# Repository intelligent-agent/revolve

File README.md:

```
    _/_/_/                                    _/                       
   _/    _/    _/_/    _/      _/    _/_/    _/  _/      _/    _/_/    
  _/_/_/    _/_/_/_/  _/      _/  _/    _/  _/  _/      _/  _/_/_/_/   
 _/    _/  _/          _/  _/    _/    _/  _/    _/  _/    _/          
_/    _/    _/_/_/      _/        _/_/    _/      _/        _/_/_/     
                                                                       
```                                                                      

## Main features
- 1GHz Single board solution using [Octavo OSB3358 SIP](https://octavosystems.com/2016/05/09/osd3358-new-era-integration/)
- 6 [TMC2130](https://www.trinamic.com/products/integrated-circuits/details/tmc2130/) stepper drivers, stall detection, overcurrent/temp
- 4 Thermistor or Thermocouple inputs (runtime configurable)
- 4 high power heater outputs
- 4 GB fast eMMC
- Optionally 2 external drivers
- [Direct coupled PRU lines](http://beagleboard.org/pru) to all drivers
- Flexible PWM on all 8 MOSFET outputs for flexible EMC passing
- 4 USB host ports, 1 USB device port
- 10/100Mbit Ethernet
- 1080p HDMI
- Smart power controls
 - Input voltage and current measurement
 - Power removed detection
 - Software defined overcurrent protecion
- Quad encoder input for filament sensor
- Buffered end stop inputs, ESD protected connectors
- 2 Servo outputs
- Inductive sensor input
- Two Grove connectors, I2C and UART

## Power management
Here is an overview of the power distribution

## 5V step down TPS54202 calculations

```python
import math
Vout = 5.1 # Output voltage
Vin = 24 # Input voltage
Iout = 2 # Output current
Kind = 0.3 # ?
Fsw = 500000 # Switching frequency
Cbulk = 10 *10**-6
u = 10**6 # micro

```

```python
L=(Vout*(Vin-Vout))/(Vin*Kind*Iout*Fsw)
print "Inductor selection:"
print "Minimum inductor size: "+str(L*10**6)+" uH"

Lout = 15*10**-6
Ilmax = math.sqrt(Iout**2 + (1/12) + ((Vout*(Vin-Vout))/(Vin*Lout*Fsw*0.8))**2)
print "RMS Inductor current "+str(Ilmax)
Ipeak = Iout + (Vout * (Vin - Vout))/(1.6*Vin*Lout*Fsw)
print "Max inductor current "+str(Ipeak)
print "Choosing NR8040T330M"

```

    Inductor selection:
    Minimum inductor size: 13.3875 uH
    RMS Inductor current 2.10904312204
    Max inductor current 2.3346875
    Choosing NR8040T330M

```python
dIout = 0.7
dVout = 0.2 # Delta voltage with dI
Vr = 0.03 # Ripple Voltage
Ir = Iout*0.3
CO1 = (2*dIout)/(Fsw*dVout)
CO2 = (1.0/(8.0*Fsw))*(1.0/(Vr/Ir))
#CO3 =
print "Input Capacitor Selection:"
print "CO1: "+str(CO1*u) + " uF"
print "CO2: "+str(CO2*u) + " uF"

#print "Minimum capacitance: "+str(CO*u)+" uF"
print "Choosing 20uF"
```

    Input Capacitor Selection:
    CO1: 14.0 uF
    CO2: 5.0 uF
    Choosing 20uF

```python
R2 = 100.0*10**3
R3 = 13.3*10**3
Vref = 0.596
Vout = Vref*((R2/R3)+1)
print "Calculation of output resistance: "
print "Vout = "+str(Vout)
```

    Calculation of output resistance:
    Vout = 5.07720300752

## Stepper drivers

Current sense resistor:

```python
R = 0.1
I = 1
U = R*I
P = U*I
print "Power dissipation: "+str(P)
```

    Power dissipation: 0.1

**Diagnostics:**
```python
$2*8 = 16$
```

* Connect together to form a single interrupt?
No, it's good to have individual pins for stallguard.

## Capacitor selection
- 100uF electrolytic capacitor is recommended. No mention of ESR or ripple current in the TMC2130 data sheet.
- What is the frequency at which the largest current draw is expected?
- There are 10uF capacitors in line to handle high frequency current draws, so it is expected that the electrolytic capacitors will handle lower frequecy draws. It depends on cable length, ESR in PSU as well.

**SPI and enable**  
* Enable pins, can it be done using SPI?
* SPI CS pins, need 8 pins at least.
    * Use Mux?
        * Increased cost. How much?
        *
    * Daisy chain?
        * What is the required time?
        * Not good for Stepper A/B. Use CN1?
        * Each transaction takes 60 us
    * Individual pins.
        * Requires 8 pins.
*

```python
print "Stepper readout time: "
a = 6.0*40/(4*10**6)
print "it takes "+str(a*u)+" us for each transaction"
```

    Stepper readout time:
    it takes 60.0 us for each transaction

## PWM calculations

**Current setting**
* Use PWM chip?
    * Costly > $1
    * board space
* Use internal reference
    * 5 bit precision

```python
print "Number of current steps on TMC2130: "+str(2**5)
```

    Number of current steps on TMC2130: 32

# Smart input current monitor circuit.
Fuses have slow responses, so they do not protect against short circuits
and only asymptotically approach their rating with time. They are temperature dependent, difficult to
replace, and physically large. They also increase manufacturing time and cost due to almost universally being
through-hole components.

 - Measure input voltage
 - Measure input current.
 - Choosing PMOS to also implement power lost detection.
 - Reverse polarity protection

```python
R = 0.001
A = 30
adc_vals = 2**12
v_adc = 1.8
v_res = R*A
Gain = 50
resolution =(v_adc/adc_vals)/R/Gain

print "Over current calculations:"
print "Max current: "+str(A)+" A"
print "Resistor value: "+str(R*1000)+" mOhm"
print "Voltage drop across resistor: "+str(v_res*1000)+" mV"
print "Voltage measured: "+str(v_res*Gain)
print "Power dissipation in Rsense: "+str(R*A*A)+" W"
print "resolution: "+str(resolution*1000)+" mA"
```

    Over current calculations:
    Max current: 30 A
    Resistor value: 1.0 mOhm
    Voltage drop across resistor: 30.0 mV
    Voltage measured: 1.5
    Power dissipation in Rsense: 0.9 W
    resolution: 8.7890625 mA

```python
v_max = 24
R1 = 100*10**3
R2 = 4.7*10**3
print "Input voltage calculations: "
print "Voltage divider max output: "+str(v_max*R2/(R1+R2))
print "Input voltage resolution: ??"
```

    Input voltage calculations:
    Voltage divider max output: 1.07736389685
    Input voltage resolution: ??

```python
Imax = 30
RDS = 5.6*10**-3
Ploss = RDS*Imax*Imax
print "Input P-mos power calculations:"
print "Power expenditure: "+str(Ploss)+ " W"
```

    Input P-mos power calculations:
    Power expenditure: 5.04 W

## ESD considerations
 - EN 55024/EN 61000-4-2: ±4kV Contact, ±8kV Air
### Board
 - Ground shield, having 0.1R to ground.
### USB
 - Using [TPD4S012](http://www.ti.com/product/TPD4S012) having Contact: ±10kV, Air: ±10kV
### HDMI
 - Using [TPD12S016](http://www.ti.com/product/TPD12S016)
### Ethernet
 - Isolated using magnetics.
### Endstops
 - Input buffer [CD4050BD](http://www.ti.com/product/CD4050BD) with HBD: ±1500, CDM: ±1000
### Analog
 - Series resistance
### Steppers
 - TMC2130 HBM: ±4 kV
### Heater MOSFETs
 - 4.7nF protection
### Fan MOSFETS
 - No protection

## Layout considerations
Using en562748 as reference for PHY layout.
 - Using 100R resistors in series to reduce EMI.
 - Placing PHY chip close to SIP since differential lines radiate less than 3.3V single ended lines.
 - Removing ground plane under magnetics.
 - 100 Ohm differential impedance
 - Place 49.9ohm pullups close to PHY chip.
 - OSH park uses FR408 laminate

```python
Er = 3.67 # Relative dielectric costant
H = 0.17018 # prepreg height in mm
T = 0.035 # Copper thickness (mm)
F = 125 # Frequency MHz
print "0.15/0.15 track and gap gives 98.4 differential and 65.3 single ended"
```

    0.15/0.15 track and gap gives 98.4 differential and 65.3 single ended

```python
Vf = 2.8 # Diode forward voltage drop (V)
Vin = 3.3 # Input voltage (V)
Vres = Vin-Vf
If = 0.0001 # Diode current, 1mA
R = Vres/If
print "LED power calculations: "
print "Resistor for {}, {}mA: {}".format(Vin, If*1000,R)
```

    LED power calculations:
    Resistor for 3.3, 0.1mA: 5000.0

# Sysboot config
Two Boot modes: MMC1 or USB device
 - SYSBOOT[15-14] = 10b = 25MHz
 - SYSBOOT[13:12] = 00b = reserved
 - SYSBOOT[11:10] = xx
 - SYSBOOT[9] = xx
 - SYSBOOT[8] = xx
 - SYSBOOT[7-6] = xx
 - SYSBOOT[5] = 0b = Disable CLKOUT1
 - SYSBOOT[4:0] = 11100b = MMC1, MMC0, UART0, USB0

 To boot from USB:
 - SYSBOOT[4:0] = 11000b = SPI0, MMCO0, USB0, UART0

```python
Imax = 1.5 # Maximum output current on all 4 USB ports
Rmeas = 0.01 # Current measurement resistor on low side.
RDSon = 0.065 #P-mos RDSon
Vin = 5.1
Vdrop = Vin - (Rmeas + RDSon)*Imax
print "Voltage drop across R: {}".format(Rmeas*Imax)
print "Resulting voltage to USB: {}".format(Vdrop)
```

    Voltage drop across R: 0.015
    Resulting voltage to USB: 4.9875

```python
Imax = 1.5 # Maximum output current on all 4 USB ports
Rmeas = 0.01 # Current measurement resistor on low side.
RDSon = 0.065 #P-mos RDSon
Vin = 5.1
Vdrop = Vin - (Rmeas + RDSon)*Imax
print "Voltage drop across R: {}".format(Rmeas*Imax)
print "Resulting voltage to USB: {}".format(Vdrop)
```

    Voltage drop across R: 0.015
    Resulting voltage to USB: 4.9875

### Review
 - Changed vias to tented
 - Moved pin 1 indicator on U2
 - Moved all test points to top side
 -

```python
from IPython.display import display, Markdown, Latex
```

## Calculation of power dissipation of P-MOS
* `$R_{ds(on)max} = 45 m\Omega$ @ $-10 V$`
* Thermal Resistance, Junction to Ambient @ `$TA=+25 ^{\circ}C$ is $R_{\theta JA}=26 ^{\circ}C/W$`

```python
Von=6
Ta=25
Imax=30
#Imax=2
Rdson=0.0045
TR=26

# P=I^2*R
P=Imax*Imax*Rdson

Trise=TR*P
T=Ta+Trise

display(Markdown("""
$P={P:0.3f} W$\n
$T_{{rise}} = {Trise} ^{{\circ}}C$\n
$T = T_A + T_{{rise}} = {T:0.3f} ^{{\circ}}C$ when $I={I:.0f} A$

""".format(P=P, Trise=Trise, T=T, I=Imax)))
```

    $P=4.050 W$

    $T_{rise} = 105.3 ^{\circ}C$

    $T = T_A + T_{rise} = 130.300 ^{\circ}C$ when $I=30 A$

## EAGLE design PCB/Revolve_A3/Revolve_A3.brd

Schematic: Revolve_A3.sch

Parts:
C1, C2, C4, C5, C6, C8, C10, C12, C13, C15, C16, C18, C19, C20, C21, C23, C24, C27, C28, C29, C30, C31, C32, C35, C38, C40, C43, C44, C53, C54, C56, C60, C61, C63, C64, C66, C67, C69, C70, C72, C73, C74, C82, C83, C84, C85, C87, C99, C107, C108, C110, C114, C115, C133, C134, C138, C140, C141, C142, C150, C151, C155: 0.1uF; C0402; MPN CL10B104KB8NNND
C3, C7, C9, C11, C39, C88, C132: 22nF; C0402; MPN C1005X7R1E223K050BB
C14, C17, C48, C80: 22uF; C1206; MPN CL31B106KAHNNNE
C22, C57, C58, C59, C102: 4.7nF; C0402; MPN CL05B472KA5NNNC
C25: 100uF; 153CLV-0605; MPN RSL0J101MCN1GB
C26, C33, C37, C45, C46, C49, C55, C65, C68, C86, C103: 4.7uF; C0402; MPN GRM155R60J475ME47D
C34, C109, C111, C112, C113: 2.2uF; C0402; MPN GRM155R61A225KE95D
C36, C146, C147, C148, C149, C156, C157: 18pF; C0402; MPN GRM0335C1E180JA01D
C41, C47, C89, C91, C92, C93, C100: 10uF,35V; C0805; MPN GRM21BR6YA106KE43K
C42, C94, C95, C97, C98, C101: 100uF,35V,0.025R; RHS1V10MCN1GS; MPN RHS1V101MCN1GS
C135, C143: 10uF,3.3V; C0805; MPN C0805C106K8PACTU
C136: 470pF; C0402; MPN CL05B471KB5NNNC
D1, D2, D3, D4, D5: MBRA340T3; SMA; MPN MBRA340T3G
EEPROM_WP: TPB1,27; B1,27
IC1, IC6, IC7: 74AHC1G126DCK; SC70-5; MPN M74VHC1GT126DF1G
IC2: CY7C65632; QFN28; MPN CY7C65632-28LTXCT
IC29: LAN8710A; 32-QFN; MPN LAN8710A-EZC-TR
IC30: MTFC2GMDEA; WFBGA; MPN EMMC04G-M627-X03R
J1: CTI-JTAG
J2, J3: 4P-2.0; HW4-2.0; MPN 1125S-4P
JP1, JP2: FIDUCIAL1X2.5; FIDUCIAL-1X2.5
L1: 15uH; NR8040T330; MPN NRS8040T150MJGJ
L2, L3: 150OHM,800mA; L2012C; MPN MU2029-151Y
LED0, LED1, LED2, LED3, LED4, LED5, LED6, LED7, LED8, LED9, LED10, LED11, LED12, LED13: blue; CHIP-LED0603; MPN 19-217/BHC-ZL1M2RY/3T
LOGO1: OSHW_LOGO_FILLX0200-NT; OSHW_FILLX200_NOTEXT
MGT1, MGT2, MGT3, MGT4: MOUNTING_HOLE
PMIC_NRESET: TPTP10R; TP10R
Q1, Q2, Q3, Q8: AON6758; 8-DFN-EP-(5X6); MPN SIRA34DP-T1-GE3
Q4, Q5, Q6, Q7, Q12: NPN-TRANSISTOR_SOT23; SOT23; MPN AO7400
Q9: MMBT2907; SOT23-BEC; MPN MMBT2907ALT3G
Q10, Q11, Q13, Q14: DMC2038LVT; TSOT26; MPN DMC2038LVT-7
R1, R2, R6, R27, R31, R35, R37, R38, R39, R40, R43, R50, R55, R56, R57, R58, R60, R73, R78, R81, R88, R90, R94, R121, R127, R128, R129, R130, R131, R132, R133, R134, R135, R136, R137, R140, R141, R147, R152: 10K,1%; R0402; MPN RC0402FR-0710KL
R3, R4, R7, R8, R9, R10, R11, R29, R30, R42, R138, R139, R149: 0.1R; R0805; MPN RL1220S-R10-F
R5, R13, R14, R15, R16, R17, R18, R19, R20, R21, R23, R24, R25, R28, R32, R33, R34, R36, R44, R46, R47, R48, R51, R54, R61, R62, R63, R64, R65, R66, R67, R68, R69, R74, R75, R76, R77, R89, R91, R92, R93, R112, R142, R143, R144, R145, R171, R172, R173: 4.7K,1%; R0402; MPN RC0402FR-074K7L
R12, R45, R84, R87, R105, R107, R108, R114, R115, R116, R117, R118, R119, R120, R174, R175, R176, R177, R178, R179: 100K,1%; R0402; MPN RC0402FR-07100KL
R22: 13.3K,1%; R0402; MPN RC0402FR-0713K3L
R26: 0.001,1%; R1206; MPN CSR1206-0R001F1
R41, R86, R148: 40.2K,1%; R0402; MPN RC0402FR-0740K2L
R49: 499; R0402; MPN RC0402FR-07499RL
R52, R59, R70, R71, R72, R126: 2.2R; R0402; MPN RC0402FR-072R2L
R53, R106, R109, R110, R111, R153, R154, R155: 1K,1%; R0402; MPN RC0402FR-071KL
R79, R80: 470; R0402; MPN RC0402JR-07470RL
R82: 12.1K, 1%; R0402; MPN RC0402FR-0712K1L
R83: 10,1%; R0402; MPN RC0402FR-0710RL
R85, R95, R96, R97, R98, R99, R100, R101, R102, R103, R104, R161, R162, R180, R181: 100; R0402; MPN RC0402FR-07100RL
R113: 649,1%; R0402; MPN RC0402FR-07649RL
R122, R123, R124, R125: 49.9,1%; R0402; MPN RC0402FR-0749R9L
R146: 47k,NTC; R0402; MPN NCP15WB473E03RC
R150: 1M; R0402; MPN RC0402JR-071ML
R151: 0,DNP; R0402; MPN RC0402FR-071KL
SV1, SV5: MA04-1
SV4, SV6: MA05-2
SYS_5V: TPTP06R; TP06R
SYS_RTC_1V8: TPB1,27; B1,27
SYS_VDD1_3V3: TPTP10R; TP10R
SYS_VDD2_3V3: TPTP11R; TP11R
SYS_VDD3_3V3: TPB1,27; B1,27
U1: OSD3358-512M-BSM; OSD335X-BGA-256; MPN OSD3358-512M-BSM
U3: TPS2061D; SOIC127P600X175-8N
U4, U6, U8, U9, U10: TPD4S012_DRY_6_P1_P; DRY6; MPN TPD4S012DRYR
U5: UA78L05ACD; SOIC127P600X175-8N; MPN UA78L12ACDR
U7: TLVH431; SOT23-3; MPN TLVH431IDBZR
U11: SN74AHC595PW; SOP65P640X120-16N
U12: APX811SOT; SOT143-R; MPN APX811-31UG-7
U13: INA199A1DCKR; SOT65P210X110-6N
U19: CD4050BD; SOIC127P600X175-16N; MPN CD4050BDR
U$2, U$9, U$13, U$14, U$15, U$16: TRINAMIC_TMC2130_QFN36; TRINAMIC_QFN36; MPN TMC2130-LA-T
U$3: LPJ0011BBNL; MPN LPJ0011BBNL
U$4: CC-BY-SA
U$5, U$6: USB-A; MPN 320010475
U$7: TDA19988BHN/C1,557; SOT804-4; MPN TDA19988BHN/C1,518
U$8: USB-MICRO; MPN ST-USB-001G-4
U$10: TPS54202; SOT23; MPN TPS54202DDCR
U$11, U$17: SISS27DN; POWERPAK-1212-8S; MPN SISS27DN-T1-GE3
U$18: TPD12S016-RKT; R-PDSO-G24; MPN TPD12S016PWR
U$19, U$20, U$21: TACT_SWITCH; DHT-1147
U$22: 445C33D24M000003.2X2.5; 403C35E12M00000; MPN ABM8G-12.000MHZ-4Y-T3
VDDS_DDR: TPTP10R; TP10R
VDDS_PLL: TPTP11R; TP11R
VDD_CODE: TPTP10R; TP10R
VDD_MPU: TPTP11R; TP11R
X1, X7, X8, X10, X11, X13, X19, X22, X29: 22-05-7038-03; 7395-03; MPN 640455-3
X2, X20: MSTBA4; MPN 39532-1004
X3, X21, X26: MSTBA2; MPN 39532-1002
X4, X5, X6, X9: 22-05-7028-02; 7395-02; MPN 640455-2
X12, X14, X15, X16, X17, X18, X25: 22-05-7048-04; 7395-04; MPN 640455-4
X24: HDMI4; HDMI-A-TH; MPN 609-4614-2-ND
Y1, Y2: 25MHz; 445C33D24M00000; MPN 445C33D25M00000

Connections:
5VIN_Y: C72.1, R59.2, U$13.26 (VCC)
5VOUT_A: C55.2, R72.1, R73.2, U$16.25 (5VOUT)
5VOUT_E: C65.2, R35.2, R71.1, U$14.25 (5VOUT)
5VOUT_H: C68.2, R31.2, R52.1, U$15.25 (5VOUT)
5VOUT_X: C86.2, R126.1, R140.2, U$2.25 (5VOUT)
5VOUT_Y: C33.2, R37.2, R59.1, U$13.25 (5VOUT)
5VOUT_Z: C37.2, R27.2, R70.1, U$9.25 (5VOUT)
+5V: C36.2, C48.1, C80.1, L1.P$1, R12.1, U1.P10 (VIN_AC), U1.R10 (VIN_AC), U1.T10 (VIN_AC)
+12V: C5.2, U5.1 (OUT), X12.4
+24V: C4.1, C6.2, C8.1, C10.1, C15.1, C16.1, C28.2, C32.2, C35.2, C38.2, C40.1, C41.1, C42.+, C54.2, C56.2, C64.2, C66.2, C67.2, C69.2, C85.2, C89.1, C91.1, C92.1, C93.1, C94.+, C95.+, C97.+, C98.+, C99.2, C100.1, C101.+, D1.C, D2.C, D3.C, D4.C, R26.1, SV4.9, SV6.9, U5.8 (IN), U13.5 (IN-), U$2.16 (VS), U$2.30 (VSA), U$2.31 (VS), U$9.16 (VS), U$9.30 (VSA), U$9.31 (VS), U$13.16 (VS), U$13.30 (VSA), U$13.31 (VS), U$14.16 (VS), U$14.30 (VSA), U$14.31 (VS), U$15.16 (VS), U$15.30 (VSA), U$15.31 (VS), U$16.16 (VS), U$16.30 (VSA), U$16.31 (VS), X3.1, X4.1, X5.1, X6.1, X9.1, X20.1, X20.2, X21.1, X26.1
+24V_FOR_5V: C1.2, C47.1, D5.C, R151.1, U$10.3 (VIN)
A7-RFU-V5: IC30.A7 (NC)
CGND: MGT1.P$1, MGT2.P$1, MGT3.P$1, MGT4.P$1, R149.2, U$3.SHD1, U$3.SHD2, U$5.A9 (SHD1), U$5.A10 (SHD2), U$5.A11 (SHD3), U$5.A12 (SHD4), U$6.A9 (SHD1), U$6.A10 (SHD2), U$6.A11 (SHD3), U$6.A12 (SHD4), U$8.P$6 (GND), U$8.P$7 (GND), U$8.P$8 (GND), U$8.P$9 (GND), U$8.P$10 (GND), U$8.P$11 (GND), X24.P$1 (GND), X24.P$2 (GND), X24.P$3 (GND), X24.P$4 (GND)
DIR_A: U1.A16 (MMC0_DAT0), U$16.7 (REFR_DIR)
DIR_B: SV6.5, U1.B15 (MMC0_CLK)
DIR_C: SV4.5, U1.R6 (GPMC_AD13)
DIR_E: U1.C4 (MCASP0_AHCLKX), U$14.7 (REFR_DIR)
DIR_H: U1.C16 (MMC0_DAT2), U$15.7 (REFR_DIR)
DIR_X: U1.A2 (MCASP0_FSX), U$2.7 (REFR_DIR)
DIR_Y: U1.B1 (MCASP0_AHCLKR), U$13.7 (REFR_DIR)
DIR_Z: U1.B3 (MCASP0_FSR), U$9.7 (REFR_DIR)
DVI_+5V: C21.1, U$18.P$13 (5V_OUT), X24.18 (+5V)
E5-RFU-V5: IC30.E5 (NC)
EEPROM_WP: EEPROM_WP.TP, U1.M2 (EEPROM_WP)
EMMC_RST: IC30.K5 (RST_N), R137.1, U1.B4 (XDMA_EVENT_INTR1)
EMMV_VCCI: C138.1, IC30.C2 (VDDIM)
EMU0: J1.13 (EMU0), R171.2, U1.E2 (EMU0)
EMU1: J1.14 (EMU1), R172.2, U1.E3 (EMU1)
ENABLE_B: SV6.3, U11.6 (QG)
ENABLE_C: SV4.3, U11.7 (QH)
ENABLE_STUFF: Q12.1 (B), R91.1, R112.2, U1.J15 (USB0_DRVVBUS)
END_STOP_X1: U1.N14 (GPMC_BEN1), U19.2 (G=A)
END_STOP_X2: U1.R12 (GPMC_A1), U19.10 (J=D)
END_STOP_X_1_IN: R61.1, U19.3 (A), X22.1
END_STOP_X_2_IN: IC6.4 (O), R64.1, U19.9 (D), X10.1
END_STOP_Y1: U1.T16 (GPMC_A11), U19.4 (H=B)
END_STOP_Y2: U1.P3 (GPMC_CSN0), U19.12 (K=E)
END_STOP_Y_1_IN: R62.1, U19.5 (B), X1.1
END_STOP_Y_2_IN: IC7.4 (O), R65.1, U19.11 (E), X19.1
END_STOP_Z1: U1.T6 (GPMC_AD14), U19.6 (I=C)
END_STOP_Z2: U1.P7 (GPMC_AD15), U19.15 (L=F)
END_STOP_Z_1_IN: R63.1, U19.7 (C), X13.1
END_STOP_Z_2_IN: R66.1, U19.14 (F), X12.1
EN_TK_A: Q14.1 (G1), Q14.3 (G2), R142.2, U11.3 (QD), X11.1
EN_TK_E: Q10.1 (G1), Q10.3 (G2), R76.2, U11.15 (QA), X29.1
EN_TK_H: Q11.1 (G1), Q11.3 (G2), R92.2, U11.1 (QB), X7.1
EN_TK_HBP: Q13.1 (G1), Q13.3 (G2), R93.2, U11.2 (QC), X8.1
FAN0: Q6.1 (B), R25.2, R34.2, U1.P12 (GPMC_A2)
FAN1: Q7.1 (B), R19.2, R33.2, U1.T13 (GPMC_A3)
FAN2: Q4.1 (B), R20.2, R32.2, U1.T4 (GPMC_AD8)
FAN3: Q5.1 (B), R5.2, R21.2, U1.P5 (GPMC_AD9)
FAULT_A: R44.1, U1.R5 (GPMC_AD10), U$16.20 (SWN_DIAG0), U$16.21 (SWP_DIAG1)
FAULT_E: R36.1, U1.T7 (GPMC_CLK), U$14.20 (SWN_DIAG0), U$14.21 (SWP_DIAG1)
FAULT_H: R51.1, U1.J14 (RMII1_REF_CLK), U$15.20 (SWN_DIAG0), U$15.21 (SWP_DIAG1)
FAULT_X: R143.2, U1.T5 (GPMC_AD11), U$2.20 (SWN_DIAG0), U$2.21 (SWP_DIAG1)
FAULT_Y: R144.2, U1.R7 (GPMC_CSN3), U$13.20 (SWN_DIAG0), U$13.21 (SWP_DIAG1)
FAULT_Z: R28.1, U1.T12 (GPMC_A0), U$9.20 (SWN_DIAG0), U$9.21 (SWP_DIAG1)
GANG: IC2.23 (GANG), R87.2
GND: C1.1, C4.2, C5.1, C6.1, C8.2, C10.2, C12.2, C13.2, C14.2, C15.2, C16.2, C17.2, C18.1, C19.2, C20.1, C21.2, C23.2, C24.2, C25.-, C26.2, C27.2, C28.1, C29.2, C30.2, C31.2, C32.1, C33.1, C34.2, C37.1, C40.2, C41.2, C42.-, C43.2, C44.2, C45.2, C46.2, C47.2, C48.2, C49.2, C53.2, C54.1, C55.1, C57.2, C58.2, C59.2, C60.2, C61.2, C63.2, C64.1, C65.1, C67.1, C68.1, C70.2, C72.2, C73.2, C74.2, C80.2, C82.2, C83.2, C84.2, C85.1, C86.1, C87.2, C89.2, C91.2, C92.2, C93.2, C94.-, C95.-, C97.-, C98.-, C100.2, C101.-, C102.2, C103.2, C108.2, C109.2, C110.2, C111.2, C112.2, C113.2, C114.2, C115.2, C132.2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
GNDA_ADC: C22.2, C107.2, C151.2, U1.A9 (AGND_ADC), U1.B9 (VREFN)
HDMI_1V8: C12.1, C29.1, C31.1, C108.1, C109.1, C110.1, C111.1, C112.1, C113.1, C114.1, C115.1, L3.1, U$7.5 (VDDDC1), U$7.14 (VDDD1(IO)(1V8)), U$7.29 (VDDDC2), U$7.35 (VDDA(1V8)), U$7.36 (VDDA3(TX)(1V8)), U$7.41 (VDDA2(TX)(1V8)), U$7.46 (VDDA1(TX)(1V8)), U$7.47 (VDDA1(PLL)(1V8)), U$7.48 (VDDA2(PLL)(1V8)), U$7.55 (VDDD2(IO)(1V8))
HDMI_HPD: U$7.31 (HPD), U$18.P$4 (HPD_A), U$18.P$5 (LS_OE)
HDMI_INT: U1.R15 (GPMC_A10), U$7.50 (INT)
HEATER_A: R74.2, R75.2, R181.2, U1.N1 (GPMC_OEN_REN)
HEATER_E: R15.2, R47.2, R161.2, U1.M1 (GPMC_ADVN_ALE)
HEATER_H: R14.2, R48.2, R162.2, U1.N3 (GPMC_BEN0_CLE)
HEATER_HBP: R16.2, R46.2, R180.2, U1.N2 (GPMC_WEN)
I2C0_SCL: U1.C10 (I2C0_SCL), U1.D10 (PMIC_SCL), U$7.52 (CSCL)
I2C0_SDA: U1.C11 (I2C0_SDA), U1.D11 (PMIC_SDA), U$7.51 (CSDA)
I2C1_SCL: J2.1, U1.B11 (UART1_TXD)
I2C1_SDA: J2.2, U1.A11 (UART1_RXD)
IREF_E: R35.1, R60.2, U$14.23 (AIN_IREF)
IREF_H: R31.1, R50.2, U$15.23 (AIN_IREF)
IREF_X: R140.1, R141.2, U$2.23 (AIN_IREF)
IREF_Y: R6.2, R37.1, U$13.23 (AIN_IREF)
IREF_Z: R27.1, R58.2, U$9.23 (AIN_IREF)
I_MEASURE: U1.C9 (AIN6), U13.6 (OUT)
LCD_D0: R116.2, U1.G3 (LCD_DATA0), U$7.15 (VPC[3])
LCD_D1: R115.2, U1.G2 (LCD_DATA1), U$7.13 (VPC[4])
LCD_D2: R120.1, U1.G1 (LCD_DATA2), U$7.12 (VPC[5])
LCD_D3: R119.1, U1.H3 (LCD_DATA3), U$7.11 (VPC[6])
LCD_D4: R118.1, U1.H2 (LCD_DATA4), U$7.10 (VPC[7]), U$21.2
LCD_D5: R117.1, U1.H1 (LCD_DATA5), U$7.7 (VPB[2])
LCD_D6: R179.2, U1.J3 (LCD_DATA6), U$7.6 (VPB[3])
LCD_D7: R178.2, U1.J2 (LCD_DATA7), U$7.3 (VPB[4])
LCD_D8: R177.2, U1.J1 (LCD_DATA8), U$7.2 (VPB[5])
LCD_D9: R176.2, U1.K3 (LCD_DATA9), U$7.1 (VPB[6])
LCD_D10: R175.2, U1.K2 (LCD_DATA10), U$7.64 (VPB[7])
LCD_D11: R174.2, U1.K1 (LCD_DATA11), U$7.60 (VPA[3])
LCD_D12: R108.2, U1.L3 (LCD_DATA12), U$7.59 (VPA[4])
LCD_D13: R107.2, U1.L2 (LCD_DATA13), U$7.58 (VPA[5])
LCD_D14: R114.1, U1.L1 (LCD_DATA14), U$7.57 (VPA[6])
LCD_D15: R105.2, U1.M3 (LCD_DATA15), U$7.56 (VPA[7])
LCD_DE: U1.E1 (LCD_AC_BIAS_EN), U$7.20 (DE/FREF)
LCD_HSYNC: U1.F2 (LCD_HSYNC), U$7.22 (HSYNC/HREF)
LCD_PCLK: U1.F1 (LCD_PCLK), U$7.4 (PCLK)
LCD_VSYNC: U1.F3 (LCD_VSYNC), U$7.21 (VSYNC/VREF)
MDIO_CLK: IC29.17 (MDC), U1.D13 (MDC)
MDIO_DATA: IC29.16 (MDIO), R85.2, U1.E13 (MDIO)
MII1_COL: R103.2, U1.F15 (MII1_COL)
MII1_CRS_DV: R104.2, U1.F14 (MII1_CRS)
MII1_RXCLK: R100.2, U1.E16 (MII1_RX_CLK)
MII1_RXD0: R99.2, U1.E14 (MII1_RXD0)
MII1_RXD1: R97.2, U1.D16 (MII1_RXD1)
MII1_RXD2: R96.2, U1.D15 (MII1_RXD2)
MII1_RXD3: R95.2, U1.D14 (MII1_RXD3)
MII1_RXDV: R98.2, U1.F16 (MII1_RX_DV)
MII1_RXERR: R101.2, U1.E15 (MII1_RX_ER)
MII1_TXCLK: R102.2, U1.H16 (MII1_TX_CLK)
MII1_TXD0: IC29.22 (TXD0), U1.H15 (MII1_TXD0)
MII1_TXD1: IC29.23 (TXD1), U1.H14 (MII1_TXD1)
MII1_TXD2: IC29.24 (TXD2), U1.G16 (MII1_TXD2)
MII1_TXD3: IC29.25 (TXD3), U1.G15 (MII1_TXD3)
MII1_TXEN: IC29.21 (TXEN), U1.G14 (MII1_TX_EN)
MMC1_CLK: IC30.M6 (CLK), R136.1, U1.P2 (GPMC_CSN1)
MMC1_CMD: IC30.M5 (CMD), R135.1, U1.P1 (GPMC_CSN2)
MMC1_DAT0: IC30.A3 (DAT0), R127.1, U1.R3 (GPMC_AD0)
MMC1_DAT1: IC30.A4 (DAT1), R128.1, U1.R2 (GPMC_AD1)
MMC1_DAT2: IC30.A5 (DAT2), R129.1, U1.R1 (GPMC_AD2)
MMC1_DAT3: IC30.B2 (DAT3), R130.1, U1.T3 (GPMC_AD3)
MMC1_DAT4: IC30.B3 (DAT4), R131.1, U1.T2 (GPMC_AD4)
MMC1_DAT5: IC30.B4 (DAT5), R132.1, U1.T1 (GPMC_AD5)
MMC1_DAT6: IC30.B5 (DAT6), R133.1, U1.P4 (GPMC_AD6)
MMC1_DAT7: IC30.B6 (DAT7), R134.1, U1.R4 (GPMC_AD7)
MODE2: IC29.15 (COL/CRS_DV/MODE2), R103.1, R155.2
unnamed: R41.1, R88.2, U7.1 (REF)
unnamed: U$13.13 (OB1), X15.3
unnamed: C3.2, U$13.27 (CPO)
unnamed: Q9.B, R49.2, U7.2 (CATHODE)
unnamed: C2.2, U$10.6 (BOOT)
unnamed: U$9.34 (OA1), X16.1
unnamed: Q12.3 (C), R86.2
unnamed: LED5.A, R19.1
unnamed: Q6.3 (C), X9.2
unnamed: C9.2, U$15.27 (CPO)
unnamed: R9.2, U$15.14 (BRB)
unnamed: C7.2, U$9.27 (CPO)
unnamed: R7.2, U$9.14 (BRB)
unnamed: U$9.32 (OA2), X16.2
unnamed: R24.2, R53.1, U$17.G
unnamed: IC2.8 (RREF), R113.1
unnamed: U$13.32 (OA2), X15.2
unnamed: U$13.34 (OA1), X15.1
unnamed: LED0.A, R25.1
unnamed: U$14.34 (OA1), X17.1
unnamed: C36.1, R12.2, R22.1, U$10.4 (FB)
unnamed: R8.2, U$9.33 (BRA)
unnamed: Q5.3 (C), X6.2
unnamed: R84.2, R86.1, U$11.G
unnamed: C7.1, U$9.28 (CPI)
unnamed: U$14.32 (OA2), X17.2
unnamed: U$9.15 (OB2), X16.4
unnamed: R10.2, U$15.33 (BRA)
unnamed: U$18.P$10 (HPD_B), X24.19 (HOT_PLUG_DETECT)
unnamed: U$15.34 (OA1), X18.1
unnamed: Q10.6 (D1), R1.1
unnamed: U1.F4 (VDDS_DDR), VDDS_DDR.TP
unnamed: R3.2, U$13.14 (BRB)
unnamed: R4.2, U$13.33 (BRA)
unnamed: U$9.13 (OB1), X16.3
unnamed: U$15.32 (OA2), X18.2
unnamed: U$14.13 (OB1), X17.3
unnamed: U1.G4 (VDD_CORE), VDD_CODE.TP
unnamed: C3.1, U$13.28 (CPI)
unnamed: LED8.A, R112.1
unnamed: R151.2, U$10.5 (EN)
unnamed: U$16.34 (OA1), X25.1
unnamed: U$13.15 (OB2), X15.4
unnamed: U$16.32 (OA2), X25.2
unnamed: Q10.4 (D2), R18.2
unnamed: C35.1, U$13.29 (VCP)
unnamed: R43.2, R73.1, U$16.23 (AIN_IREF)
unnamed: Q13.6 (D1), R56.1
unnamed: C38.1, U$9.29 (VCP)
unnamed: Q14.6 (D1), R57.1
unnamed: U$18.P$9 (SDA_B), X24.16 (SDA)
unnamed: U$18.P$8 (SCL_B), X24.15 (SCL)
unnamed: U$18.P$7 (CEC_B), X24.13 (CEC)
unnamed: Q11.4 (D2), R17.2
unnamed: Q13.4 (D2), R13.2
unnamed: Q14.4 (D2), R77.2
unnamed: C57.1, D3.A, Q2.5 (D), Q2.6 (D), Q2.7 (D), Q2.8 (D), Q2.TH (D), X21.2
unnamed: Q11.6 (D1), R55.1
unnamed: Q3.4 (G), R161.1
unnamed: Q2.4 (G), R162.1
unnamed: C39.2, U$14.27 (CPO)
unnamed: R29.2, U$14.14 (BRB)
unnamed: R30.2, U$14.33 (BRA)
unnamed: Q1.4 (G), R180.1
unnamed: IC1.2 (I), U1.N12 (PMIC_PGOOD), U1.P11 (PWRONRSTN)
unnamed: C39.1, U$14.28 (CPI)
unnamed: IC1.1 (OE), R2.2, U$19.4
unnamed: U$14.15 (OB2), X17.4
unnamed: IC1.4 (O), R90.1, U12.3 (MR#)
unnamed: C66.1, U$14.29 (VCP)
unnamed: Q8.4 (G), R181.1
unnamed: C9.1, U$15.28 (CPI)
unnamed: U$15.15 (OB2), X18.4
unnamed: C11.2, U$16.27 (CPO)
unnamed: C69.1, U$15.29 (VCP)
unnamed: C73.1, R70.2, U$9.26 (VCC)
unnamed: U$15.13 (OB1), X18.3
unnamed: Q4.3 (C), X5.2
unnamed: Q7.3 (C), X4.2
unnamed: LED6.A, R20.1
unnamed: LED7.A, R21.1
unnamed: LED9.A, R23.1
unnamed: LED10.A, R67.1
unnamed: LED11.A, R68.1
unnamed: LED12.A, R69.1
unnamed: R11.2, U$16.14 (BRB)
unnamed: LED3.A, R15.1
unnamed: R42.2, U$16.33 (BRA)
unnamed: LED1.A, R14.1
unnamed: LED2.A, R16.1
unnamed: C11.1, U$16.28 (CPI)
unnamed: U$16.15 (OB2), X25.4
unnamed: C56.1, U$16.29 (VCP)
unnamed: C60.1, R72.2, U$16.26 (VCC)
unnamed: U$16.13 (OB1), X25.3
unnamed: LED4.A, R74.1
unnamed: C102.1, D4.A, Q8.5 (D), Q8.6 (D), Q8.7 (D), Q8.8 (D), Q8.TH (D), X26.2
unnamed: R77.1, R78.1, X11.2
unnamed: R79.1, U$3.11 (YELC)
unnamed: R80.1, U$3.10 (GRNC)
unnamed: IC29.3 (LED1/REGOFF), U$3.9 (GRNA)
unnamed: IC29.2 (LED2/NINTSEL), R121.1, U$3.12 (YELA)
unnamed: PMIC_NRESET.TP, U1.M13 (PMIC_NRESET)
unnamed: IC29.18 (NINT/TXER/TXD4), R81.2
unnamed: IC29.32 (RBIAS), R82.2
unnamed: C87.1, R126.2, U$2.26 (VCC)
unnamed: C88.2, U$2.27 (CPO)
unnamed: U$7.30 (CEC), U$18.P$1 (CEC_A)
unnamed: C88.1, U$2.28 (CPI)
unnamed: C99.1, U$2.29 (VCP)
unnamed: R138.2, U$2.14 (BRB)
unnamed: R139.2, U$2.33 (BRA)
unnamed: C146.2, R150.1, U1.P16 (OSC0_IN), Y1.P$1
unnamed: C146.1, C147.1, U1.N15 (OSC0_GND)
unnamed: U1.T11 (PMIC_PB_IN), U$20.2
unnamed: C148.1, IC29.5 (XTAL1/CLKIN), Y2.P$2
unnamed: C149.1, R83.2, Y2.P$1
unnamed: IC29.4 (XTAL2), R83.1
unnamed: C147.2, R150.2, U1.N16 (OSC0_OUT), Y1.P$2
unnamed: LED13.A, R89.1
unnamed: R94.1, U$7.34 (EXT_SWING)
unnamed: IC29.26 (RXDV), R98.1
unnamed: IC29.20 (TXCLK), R102.1
unnamed: C59.1, D1.A, Q3.5 (D), Q3.6 (D), Q3.7 (D), Q3.8 (D), Q3.TH (D), X3.2
unnamed: R13.1, R38.1, X8.2
unnamed: R18.1, R40.1, X29.2
unnamed: R17.1, R39.1, X7.2
unnamed: C58.1, D2.A, Q1.5 (D), Q1.6 (D), Q1.7 (D), Q1.8 (D), Q1.TH (D), X20.3, X20.4
unnamed: IC29.14 (CRS), R104.1
P-SHUNT: R26.2, U13.4 (IN+), U$11.D1 (D), U$11.D2 (D), U$11.D3 (D), U$11.D4 (D), U$11.D5 (D)
PMIC_LDO_PGOOD: U1.N4 (PMIC_LDO_PGOOD), U1.N5 (RTC_PWRONRSTN)
PMIC_MUX: U1.C8 (AIN5), U1.D6 (PMIC_MUX_OUT)
PMIC_NINT: U1.D4 (EXTINTN), U1.E4 (PMIC_NINT)
PMIC_NWAKEUP: U1.L4 (PMIC_NWAKEUP), U1.M4 (EXT_WAKEUP)
PMIC_PWR_EN: U1.N10 (PMIC_POWER_EN), U1.N11 (PMIC_PWR_EN)
QUAD_ENCODER_A: SV5.3, U1.R13 (GPMC_A4)
QUAD_ENCODER_B: SV5.2, U1.P13 (GPMC_A5)
REFCLK0: IC29.7 (RXCLK/PHYAD1), R100.1, R106.2
RTC_KALDO_ENN: R152.1, U1.M16 (RTC_KALDO_ENN)
RXD0: IC29.11 (RXD0/MODE0), R99.1, R153.2
RXD1: IC29.10 (RXD1/MODE1), R97.1, R154.2
RXD2: IC29.9 (RXD2/RMIISEL), R96.1, R109.2
RXD3: IC29.8 (RXD3/PHYAD2), R95.1, R110.2
RXER: IC29.13 (RXER/RXD4/PHYAD0), R101.1, R111.2
RXN: IC29.30 (RXN), R122.2, U$3.2 (RD-)
RXP: IC29.31 (RXP), R123.2, U$3.1 (RD+)
SCL_A: U$7.33 (DSCL), U$18.P$2 (SCL_A)
SDA_A: U$7.32 (DSDA), U$18.P$3 (SDA_A)
SERVO_0: IC6.2 (I), SV1.3, U1.B12 (UART0_TXD)
SERVO_0_EN: IC6.1 (OE), U11.4 (QE)
SERVO_1: IC7.2 (I), SV1.4, U1.A12 (UART0_RXD)
SERVO_1_EN: IC7.1 (OE), U11.5 (QF)
SPI0_CS0: U1.A14 (SPI0_CS0), U$2.2 (CSN_CFG3), U$9.2 (CSN_CFG3), U$13.2 (CSN_CFG3), U$14.2 (CSN_CFG3), U$15.2 (CSN_CFG3), U$16.2 (CSN_CFG3)
SPI0_CS1: U1.C14 (SPI0_CS1), U11.12 (RCLK)
SPI0_MISO: U1.B13 (SPI0_D0), U$16.5 (SDO_NAO_CFG0)
SPI0_MISO_E: U$14.5 (SDO_NAO_CFG0), U$15.4 (SDI_NAI_CFG1)
SPI0_MISO_H: U$15.5 (SDO_NAO_CFG0), U$16.4 (SDI_NAI_CFG1)
SPI0_MISO_X: U$2.5 (SDO_NAO_CFG0), U$13.4 (SDI_NAI_CFG1)
SPI0_MISO_Y: U$9.4 (SDI_NAI_CFG1), U$13.5 (SDO_NAO_CFG0)
SPI0_MISO_Z: U$9.5 (SDO_NAO_CFG0), U$14.4 (SDI_NAI_CFG1)
SPI0_MOSI: U1.B14 (SPI0_D1), U11.14 (SER), U$2.4 (SDI_NAI_CFG1)
SPI0_SCLK: U1.A13 (SPI0_SCLK), U11.11 (SRCLK), U$2.3 (SCK_CFG2), U$9.3 (SCK_CFG2), U$13.3 (SCK_CFG2), U$14.3 (SCK_CFG2), U$15.3 (SCK_CFG2), U$16.3 (SCK_CFG2)
SPI1_CS0: SV4.4, U1.B10 (UART1_CTSN)
SPI1_CS1: SV6.4, U1.A10 (UART1_RTSN)
SPI1_MISO: SV4.6, SV6.6, U1.C12 (UART0_CTSN)
SPI1_MOSI: SV4.8, SV6.8, U1.C13 (UART0_RTSN)
SPI1_SCLK: SV4.2, SV6.2, U1.C5 (ECAP0_IN_PWM0_OUT)
STEP_A: U1.A15 (MMC0_DAT1), U$16.6 (REFL_STEP)
STEP_B: SV6.7, U1.B16 (MMC0_CMD)
STEP_C: SV4.7, U1.P6 (GPMC_AD12)
STEP_E: U1.C3 (MCASP0_AXR1), U$14.6 (REFL_STEP)
STEP_H: U1.C15 (MMC0_DAT3), U$15.6 (REFL_STEP)
STEP_X: U1.A1 (MCASP0_ACLKX), U$2.6 (REFL_STEP)
STEP_Y: U1.B2 (MCASP0_AXR0), U$13.6 (REFL_STEP)
STEP_Z: U1.A3 (MCASP0_ACLKR), U$9.6 (REFL_STEP)
SW: C2.1, L1.P$2, U$10.2 (SW)
SYS_5V: C18.2, C19.1, C24.1, C25.+, C82.1, C83.1, IC6.5 (VCC), IC7.5 (VCC), R61.2, R62.2, R63.2, R64.2, R65.2, R66.2, R147.2, SYS_5V.TP, U1.K6 (SYS_VOUT), U1.K7 (SYS_VOUT), U1.L6 (SYS_VOUT), U1.L7 (SYS_VOUT), U1.M15 (USB1_VBUS), U3.2 (IN_2), U3.3 (IN), U11.10 (~SRCLR), U11.16 (VCC), U$18.P$11 (VCC5V), X1.3, X10.3, X12.3, X13.3, X19.3, X22.3
SYS_RESETN: IC29.19 (NRST), U1.R11 (WARMRSTN), U12.2 (RESET#)
SYS_RTC_1V8: Q9.C, R41.2, SYS_RTC_1V8.TP, U1.K11 (SYS_RTC_1P8V), U1.L11 (SYS_RTC_1P8V), U7.3 (ANODE)
SYS_VDD1_3V3: C13.1, C20.2, C23.1, C27.1, C30.1, C43.1, C44.1, C53.1, C61.1, C63.1, C84.1, C140.1, C141.1, C142.1, C143.1, C150.1, C155.1, IC1.5 (VCC), IC2.5 (VCC_A), IC2.9 (VCC_A), IC2.14 (VCC_A), IC2.21 (VCC_D), IC2.22 (SELFPWR), IC2.28 (VREG), IC29.12 (VDDIO), IC30.C6 (VCCQ), IC30.E6 (VCC), IC30.F5 (VCC), IC30.J10 (VCC), IC30.K9 (VCC), IC30.M4 (VCCQ), IC30.N4 (VCCQ), IC30.P3 (VCCQ), IC30.P5 (VCCQ), J1.5 (TVDD), L2.1, R2.1, R28.2, R36.2, R44.2, R51.2, R85.1, R87.1, R105.1, R118.2, R119.2, R120.2, R127.2, R128.2, R129.2, R130.2, R131.2, R132.2, R133.2, R134.2, R135.2, R136.2, R137.2, R143.1, R144.1, R153.1, R154.1, R155.1, R171.1, R172.1, SYS_VDD1_3V3.TP, U1.F6 (SYS_VDD1_3P3V), U1.F7 (SYS_VDD1_3P3V), U1.G6 (SYS_VDD1_3P3V), U1.G7 (SYS_VDD1_3P3V), U12.4 (VCC), U13.3 (V+), U19.1 (VCC), U$2.8 (VCC_IO), U$9.8 (VCC_IO), U$13.8 (VCC_IO), U$14.8 (VCC_IO), U$15.8 (VCC_IO), U$16.8 (VCC_IO), U$18.P$12 (CT_HPD), U$18.P$24 (VCCA)
SYS_VDD2_3V3: J2.3, J3.3, R89.2, SV1.2, SV4.10, SV5.4, SV6.10, SYS_VDD2_3V3.TP, U1.F11 (SYS_VDD2_3P3V), U1.G11 (SYS_VDD2_3P3V)
SYS_VDD3_3V3: Q9.E, R49.1, R88.1, SYS_VDD3_3V3.TP, U1.F8 (SYS_VDD3_3P3V), U1.F9 (VDDSHV4), U1.G8 (SYS_VDD3_3P3V), U1.G9 (VDDSHV5), U1.H7 (SYS_VDD3_3P3V), U1.H8 (SYS_VDD3_3P3V), U1.H9 (VDDSHV6), U1.J7 (SYS_VDD3_3P3V), U1.J8 (SYS_VDD3_3P3V), U1.J9 (VDDSHV1), U1.K8 (SYS_VDD3_3P3V), U1.K9 (VDDSHV2), U1.L8 (SYS_VDD3_3P3V), U1.L9 (VDDSHV3)
SYS_VDD_1V8: L3.2, U1.F10 (SYS_VDD_1P8V), U1.G10 (SYS_VDD_1P8V), U1.H10 (SYS_VDD_1P8V), U1.H11 (SYS_VDD_1P8V), U1.J10 (SYS_VDD_1P8V), U1.J11 (SYS_VDD_1P8V), U1.K10 (SYS_VDD_1P8V), U1.L10 (SYS_VDD_1P8V)
TCK: J1.9 (TCKRTN), J1.11 (TCK), U1.D1 (TCK)
TDI: J1.3 (TDI), U1.C1 (TDI)
TDO: J1.7 (TDO), U1.C2 (TDO)
TERM_A: C103.1, R57.2, R78.2, U1.C6 (AIN3)
TERM_E: C46.1, R1.2, R40.2, U1.A8 (AIN0)
TERM_H: C26.1, R38.2, R56.2, U1.B6 (AIN2)
TERM_HBP: C45.1, R39.2, R55.2, U1.B8 (AIN1)
THERM_BOARD: R145.2, R146.1, U1.C7 (AIN4)
TMS: J1.1 (TMS), U1.D2 (TMS)
TRSTN: J1.2 (TRSTN), R173.1, U1.D3 (TRSTN)
TX0+: U$7.40 (TX0+), U$18.P$18 (D0+), X24.7 (TMDS_DATA0+)
TX0-: U$7.39 (TX0-), U$18.P$17 (D0-), X24.9 (TMDS_DATA0-)
TX1+: U$7.43 (TX1+), U$18.P$21 (D1+), X24.4 (TMDS_DATA1+)
TX1-: U$7.42 (TX1-), U$18.P$20 (D1-), X24.6 (TMDS_DATA1-)
TX2+: U$7.45 (TX2+), U$18.P$23 (D2+), X24.1 (TDMS_DATA2+)
TX2-: U$7.44 (TX2-), U$18.P$22 (D2-), X24.3 (TMDS_DATA2-)
TXC+: U$7.38 (TXC+), U$18.P$16 (CLK+), X24.10 (TMDS_CLOCK+)
TXC-: U$7.37 (TXC-), U$18.P$15 (CLK-), X24.12 (TMDS_CLOCK-)
TXN: IC29.28 (TXN), R124.2, U$3.6 (TD-)
TXP: IC29.29 (TXP), R125.2, U$3.3 (TD+)
UART4_RXD: J3.1, U1.P15 (GPMC_WAIT0)
UART4_TXD: J3.2, U1.R16 (GPMC_WPN)
USB0_DM: U1.K16 (USB0_DM), U10.1 (D+), U$8.P$2 (2)
USB0_DP: U1.K15 (USB0_DP), U10.2 (D-), U$8.P$3 (3)
USB0_ID: U1.K14 (USB0_ID), U10.3 (ID), U$8.P$4 (4)
USB1_DM: IC2.1 (D–), U1.L16 (USB1_DM)
USB1_DM1: IC2.3 (DD–[1]), U9.2 (D-), U$5.2 (D-)
USB1_DM2: IC2.6 (DD–[2]), U6.2 (D-), U$5.6 (D-)
USB1_DM3: IC2.12 (DD–[3]), U4.2 (D-), U$6.2 (D-)
USB1_DM4: IC2.15 (DD–[4]), U8.2 (D-), U$6.6 (D-)
USB1_DP: IC2.2 (D+), U1.L15 (USB1_DP)
USB1_DP1: IC2.4 (DD+[1]), U9.1 (D+), U$5.3 (D+)
USB1_DP2: IC2.7 (DD+[2]), U6.1 (D+), U$5.7 (D+)
USB1_DP3: IC2.13 (DD+[3]), U4.1 (D+), U$6.3 (D+)
USB1_DP4: IC2.16 (DD+[4]), U8.1 (D+), U$6.7 (D+)
USB1_DRVVBUS: U1.M14 (USB1_DRVVBUS)
USB_DC: U1.J16 (USB0_VBUS), U1.P9 (VIN_USB), U1.R9 (VIN_USB), U1.T9 (VIN_USB), U10.6 (VBUS), U$8.P$1 (1)
USB_OC: IC2.25 (OVR#[1]), U3.5 (~OC)
USB_OUT: C14.1, C17.1, U3.6 (OUT_2), U3.7 (OUT_3), U3.8 (OUT), U4.6 (VBUS), U6.6 (VBUS), U8.6 (VBUS), U9.6 (VBUS), U$5.1 (VBUS), U$5.5 (VBUS), U$6.1 (VBUS), U$6.5 (VBUS)
USB_PWR_EN: IC2.26 (I2C_SDA), U3.4 (~EN+)
USB_RESET: C49.1, IC2.17 (RESET#), R147.1, R148.1
USB_XTAL1: C157.2, IC2.10 (XIN), U$22.P$1
USB_XTAL2: C156.2, IC2.11 (XOUT), U$22.P$3
USR0: R69.2, U1.T15 (GPMC_A9)
USR1: R68.2, U1.T14 (GPMC_A6)
USR2: R67.2, U1.R14 (GPMC_A7)
USR3: R23.2, U1.P14 (GPMC_A8)
VCC: IC2.27 (VCC)
VCC_E: C74.1, R71.2, U$14.26 (VCC)
VCC_H: C70.1, R52.2, U$15.26 (VCC)
VDDCR: C34.1, C136.1, IC29.6 (VDDCR)
VDDS_PLL: U1.G13 (VDDS_PLL), VDDS_PLL.TP
VDD_ADC: C22.1, C107.1, C151.1, Q10.2 (S2), Q11.2 (S2), Q13.2 (S2), Q14.2 (S2), R145.1, U1.A7 (SYS_ADC_1P8V), U1.B7 (VREFP)
VDD_MPU: U1.F13 (VDD_MPU), VDD_MPU.TP
VDD_PHYA: C132.1, C133.1, C134.1, C135.1, IC29.1 (VDD2A), IC29.27 (VDD1A), L2.2, R122.1, R123.1, R124.1, R125.1, U$3.4 (RCT), U$3.5 (TCT)
VIN: D5.A, R45.1, U$17.D1 (D), U$17.D2 (D), U$17.D3 (D), U$17.D4 (D), U$17.D5 (D), X2.3, X2.4
VIN_BAT: U1.P8 (VIN_BAT), U1.R8 (VIN_BAT), U1.T8 (VIN_BAT)
VIN_MEASURE: R45.2, R54.1, U1.D7 (AIN7)
VMID: R24.1, R84.1, U$11.S1 (S), U$11.S2 (S), U$11.S3 (S), U$17.S1 (S), U$17.S2 (S), U$17.S3 (S)
X_A1: U$2.34 (OA1), X14.1
X_A2: U$2.32 (OA2), X14.2
X_B1: U$2.13 (OB1), X14.3
X_B2: U$2.15 (OB2), X14.4

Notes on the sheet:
Fan drivers
Power in
5V step down converter
MOSFET E
MOSFET HBP
MOSFET H
End stops 2
Thermistors
End stops 1
MOSFET A
RESET
POWER
McASP is disabled.
USB
LAN
HDMI
FANS+End stops
PWM etc
Power
eMMC
STP H/A
STP Z/E
STP X/Y
SIP LCD + LAN
Ext driver B
Ext driver C
Analog etc
R151 can be populated with 0R if TPS54202H is used instead of TPS54202

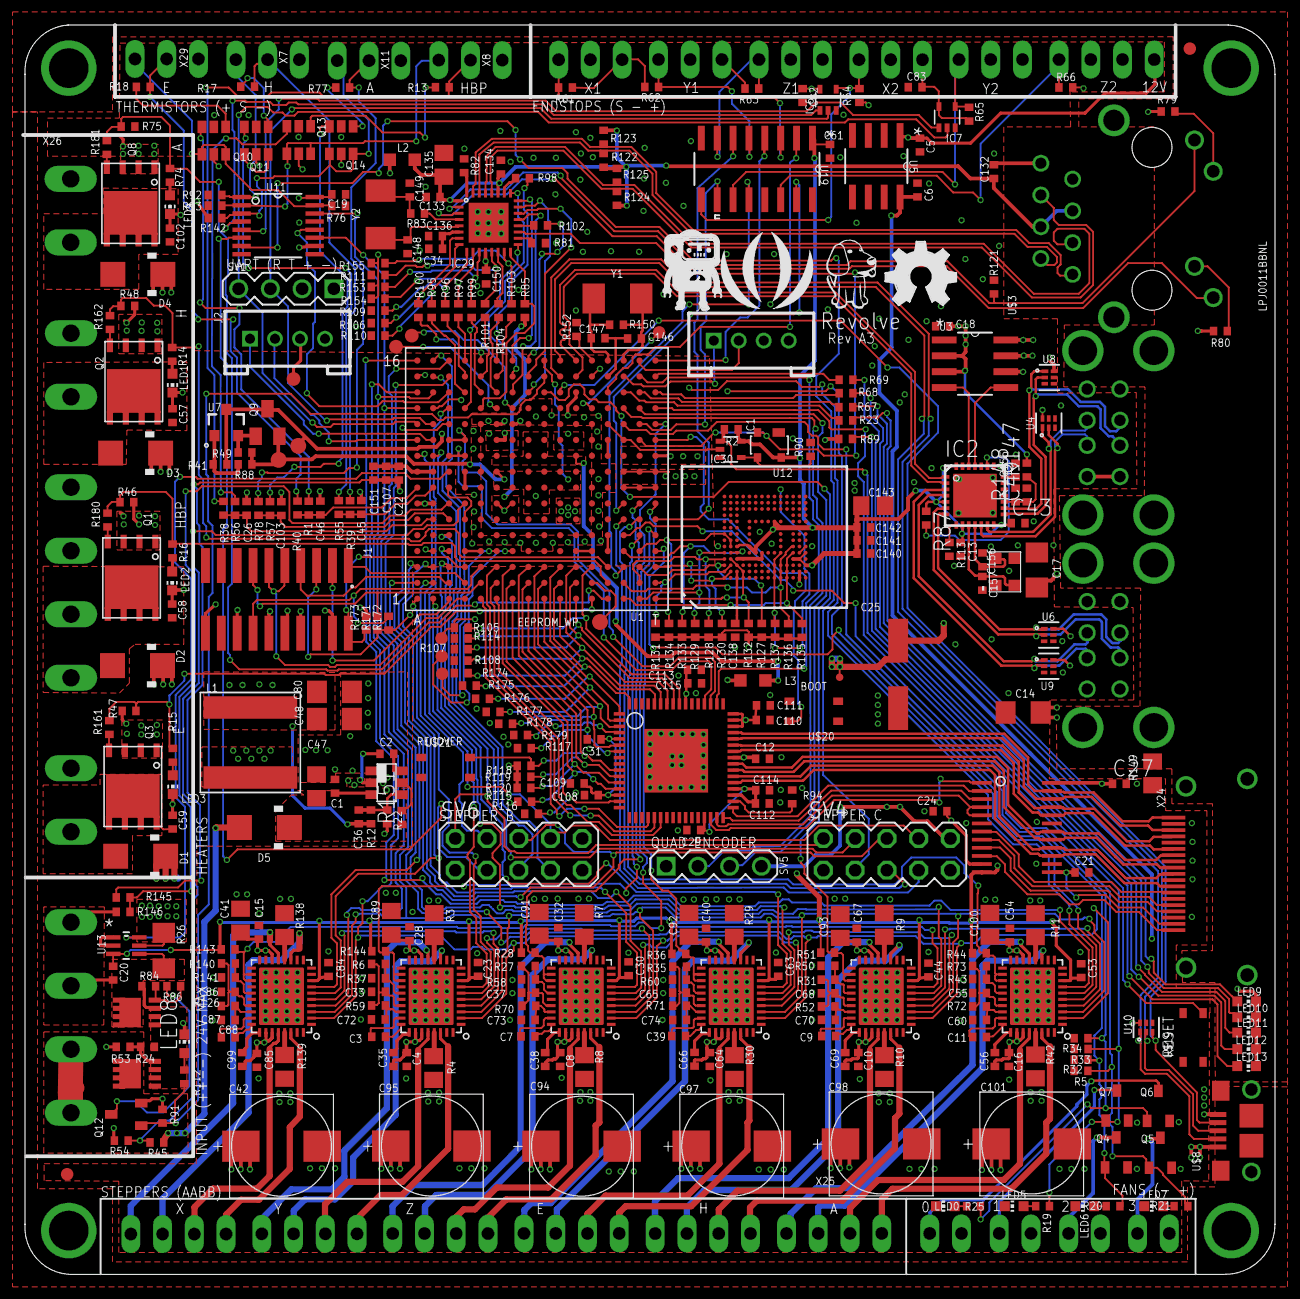
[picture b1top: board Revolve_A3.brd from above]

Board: 4 copper layers, 100.0 x 100.0 mm, 417 parts (0 on the bottom side), 367 nets.

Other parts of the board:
U$1: LOGO_BIG
U$12: BB-LOGO
U$23: S_LOGO

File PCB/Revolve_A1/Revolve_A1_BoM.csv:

Qty,Value,Part Num,Package,Parts
5,,AO7400,SOT23,"Q4, Q5, Q6, Q7, Q12"
1,,RSL0J101MCN1GB,153CLV-0605,C25
1,"0.001,1%",ERJ-MP2MF1M0U,R1206,R26
13,0.1R,RL1220S-R10-F,R0805,"R3, R4, R7, R8, R9, R10, R11, R29, R30, R42, R138, R139, R149"
61,0.1uF,GRM155R71H104KE14J,C0402,"C1, C2, C4, C5, C6, C8, C10, C12, C13, C15, C16, C18, C19, C20, C21, C23, C24, C27, C28, C29, C30, C31, C32, C35, C38, C40, C44, C53, C54, C56, C60, C61, C63, C64, C66, C67, C69, C70, C72, C73, C74, C82, C83, C84, C85, C87, C99, C107, C108, C110, C114, C115, C133, C134, C138, C140, C141, C142, C150, C151, C155"
8,"1K,1%",RC0402FR-071KL,R0402,"R53, R106, R109, R110, R111, R153, R154, R155"
1,1M,RC0402JR-071ML,R0402,R150
6,2.2R,RC0402FR-072R2L,R0402,"R52, R59, R70, R71, R72, R126"
5,2.2uF,GRM155R61A225KE95D,C0402,"C34, C109, C111, C112, C113"
49,"4.7K,1%",RC0402FR-074K7L,R0402,"R5, R13, R14, R15, R16, R17, R18, R19, R20, R21, R23, R24, R25, R28, R32, R33, R34, R36, R44, R46, R47, R48, R51, R54, R61, R62, R63, R64, R65, R66, R67, R68, R69, R74, R75, R76, R77, R89, R91, R92, R93, R112, R142, R143, R144, R145, R171, R172, R173"
5,4.7nF,CL05B472KA5NNNC,C0402,"C22, C57, C58, C59, C102"
10,4.7uF,GRM155R60J475ME47D,C0402,"C26, C33, C37, C45, C46, C55, C65, C68, C86, C103"
2,4P-2.0,1125S-4P,HW4-2.0,"J2, J3"
1,6 MHz,NX8045GB-6MHZ-STD-CSF-3,NX8045GB-6MHZ-STD-CSF-3,Y4
1,"10,1%",RC0402FR-0710RL,R0402,R83
40,"10K,1%",RC0402FR-0710KL,R0402,"R1, R2, R6, R27, R31, R35, R37, R38, R39, R40, R43, R50, R55, R56, R57, R58, R60, R73, R78, R81, R87, R88, R90, R94, R113, R121, R127, R128, R129, R130, R131, R132, R133, R134, R135, R136, R137, R140, R141, R152"
2,"10uF,3.3V",C0805C106K8PACTU,C0805,"C135, C143"
7,"10uF,35V",GMK325BJ106MN-T,C0805,"C41, C47, C89, C91, C92, C93, C100"
1,"12.1K, 1%",RC0402FR-0712K1L,R0402,R82
1,"13.3K,1%",RC0402FR-0713K3L,R0402,R22
8,"15K,1%",RC0402FR-0715KL,R0402,"R163, R164, R165, R166, R167, R168, R169, R170"
1,15uH,NRS8040T150MJGJ,NR8040T330,L1
7,18pF,GRM1555C1H180JA01D,C0402,"C36, C146, C147, C148, C149, C156, C157"
4,22-05-7028-02,640455-2,7395-02,"X4, X5, X6, X9"
9,22-05-7038-03,640455-3,7395-03,"X1, X7, X8, X10, X11, X13, X19, X22, X29"
7,22-05-7048-04,640455-4,7395-04,"X12, X14, X15, X16, X17, X18, X25"
8,"22R,1%",RC0402FR-0722RL,R0402,"R147, R148, R151, R156, R157, R158, R159, R160"
7,22nF,C1005X7R1E223K050BB,C0402,"C3, C7, C9, C11, C39, C88, C132"
4,22uF,CL31B106KAHNNNE,C1206,"C14, C17, C48, C80"
2,25MHz,445C33D25M00000,445C33D24M00000,"Y1, Y2"
2,"40.2K,1%",RC0402FR-0740K2L,R0402,"R41, R86"
1,"47k,NTC",NCP15WB473E03RC,R0402,R146
4,"49.9,1%",RC0402FR-0749R9L,R0402,"R122, R123, R124, R125"
3,74AHC1G126DCK,M74VHC1GT126DF1G,SC70-5,"IC1, IC6, IC7"
15,100,RC0402FR-07100RL,R0402,"R85, R95, R96, R97, R98, R99, R100, R101, R102, R103, R104, R161, R162, R180, R181"
19,"100K,1%",RC0402FR-07100KL,R0402,"R12, R45, R84, R105, R107, R108, R114, R115, R116, R117, R118, R119, R120, R174, R175, R176, R177, R178, R179"
6,"100uF,35V,0.025R",RHS1V101MCN1GS,RHS1V10MCN1GS,"C42, C94, C95, C97, C98, C101"
2,"150OHM,800mA",MU2029-151Y,L2012C,"L2, L3"
2,470,RC0402JR-07470RL,R0402,"R79, R80"
1,470pF,CL05B471KB5NNNC,C0402,C136
1,499,RC0402FR-07499RL,R0402,R49
4,AON6758,SIRA34DP-T1-GE3,8-DFN-EP-(5X6),"Q1, Q2, Q3, Q8"
1,APX811SOT,*,SOT143-R,U12
1,CD4050BD,CD4050BDR,SOIC127P600X175-16N,U19
4,DMC2038LVT,DMC2038LVT-7,TSOT26,"Q10, Q11, Q13, Q14"
1,HDMI4,10029449-111RLF,HDMI-A-TH,X24
1,INA199A1DCKR,INA199A1DCKR,SOT65P210X110-6N,U13
1,LAN8710A,LAN8710A-EZC-TR,32-QFN,IC29
1,LPJ0011BBNL,LPJ0011BBNL,LPJ0011BBNL,U$3
5,MBRA340T3,MBRA340T3G,SMA,"D1, D2, D3, D4, D5"
1,MMBT2907,MMBT2907ALT3G,SOT23-BEC,Q9
4,MOUNTING_HOLE,*,MOUNTING_HOLE,"MGT1, MGT2, MGT3, MGT4"
3,MSTBA2,39532-1002,MSTBA2,"X3, X21, X26"
2,MSTBA4,39532-1004,MSTBA4,"X2, X20"
1,MTFC2GMDEA,MTFC2GMDEA-0M WT,WFBGA,IC30
1,OSD3358-512M-BSM,OSD3358-512M-BSM,OSD335X-BGA-256,U1
1,OSHW_LOGO_FILLX0200-NT,*,OSHW_FILLX200_NOTEXT,LOGO1
2,SISS27DN,SISS27DN-T1-GE3,POWERPAK-1212-8S,"U$11, U$17"
1,SN74AHC595PW,SN74AHC595PW,SOP65P640X120-16N,U11
3,TACT_SWITCH,*,DHT-1147,"U$19, U$20, U$21"
1,"TDA19988BHN/C1,557","TDA19988BHN/C1,518",SOT804-4,U$7
1,TLVH431,TLVH431IDBZR,SOT23-3,U7
5,TPD4S012_DRY_6_P1_P,TPD4S012DRYR,DRY6,"U4, U6, U8, U9, U10"
1,TPD12S016-RKT,TPD12S016PWR,R-PDSO-G24,U$18
1,TPS2061D,TPS2061D,SOIC127P600X175-8N,U3
1,TPS54202,TPS54202DDCR,SOT23,U$10
6,TRINAMIC_TMC2130_QFN36,TMC2130-LA-T,TRINAMIC_QFN36,"U$2, U$9, U$13, U$14, U$15, U$16"
1,TUSB2046BIRHBT,TUSB2046BIRHBT,QFN50P500X500X100-33N,U2
1,UA78L05ACD,UA78L12ACDR,SOIC127P600X175-8N,U5
2,USB-A,320010475,USB-A,"U$5, U$6"
1,USB-MICRO,ST-USB-001G-4,USB-MICRO,U$8
14,blue,19-217/BHC-ZL1M2RY/3T,CHIP-LED0603,"LED0, LED1, LED2, LED3, LED4, LED5, LED6, LED7, LED8, LED9, LED10, LED11, LED12, LED13"

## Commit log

2016-11-20 Added notes
2016-11-20 Not finished
2017-10-03 Starting up work again
2017-10-07 Started porting to SIP-SM, changed to TMC2130
2017-10-08 New Step down, moved some stuff around
2017-10-14 Working on the LAN layout
2017-10-18 Working on layout
2017-10-21 Almost done with schematic
2017-10-22 Almost done routing. Switched to high side measurement of current
2017-10-25 Working on DRC errors
2017-10-25 DRC done, time to start documentation
2017-10-26 REady for board review
2017-10-26 Added readme
2017-10-26 Adde dimages
2017-10-26 Fixing images I hope
2017-10-28 Added calculations on PMOS to readme
2017-10-31 Ordered PCB and stencil + parts from OSH park/Digi key
2017-12-07 Adding current DT
2018-03-29 Adding rev A1
2018-04-07 readability cleanups
    - add png version of svg; I don't think the svg can be served from github reliably, so this version will show on the readme.
    - fixed links and converted to [relative links](https://help.github.com/articles/about-readmes/#relative-links-and-image-paths-in-readme-files); works for cloned/forked and also for non-master branch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
    - go through the readme to copyedit and fix markdown
    svg conversion:
    docker run -v `pwd`:/opt/app/ kevinsimper/wkhtmltoimage /opt/app/Revolve_power_diagram.svg /opt/app/revolve_power_diagra
    m.png
2018-10-24 Uploading Rev A2
2018-10-29 Adding Rev A3, revision used for first prototype run
2019-04-18 Added a design with a new input stage. Also added a project for doing spice simulations
2019-06-17 Added files needed for Umikaze.
